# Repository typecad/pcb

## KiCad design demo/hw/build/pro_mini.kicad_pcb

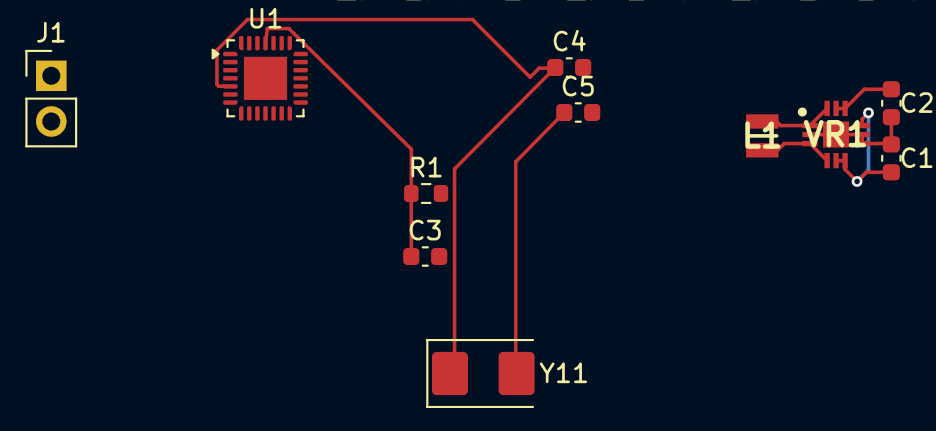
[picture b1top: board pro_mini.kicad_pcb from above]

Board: 2 copper layers, 11 parts (0 on the bottom side), 10 nets.

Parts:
C1: 22 uF; C_0603_1608Metric
C2: 10 uF; C_0603_1608Metric
C3: 100nF; C_0603_1608Metric
C4, C5: 22pF; C_0603_1608Metric
J1: PinHeader_1x02_P2.54mm_Vertical
L1: 1 µH; 1285ASH1R0MP2
R1: 10k; R_0603_1608Metric
U1: QFN-28-1EP_4x4mm_P0.45mm_EP2.4x2.4mm
VR1: QFN50P300X300X75-13N-D
Y11: Crystal_SMD_5032-2Pin_5.0x3.2mm

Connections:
net1: C1.2, VR1.5, VR1.6
net2: C1.1, C2.2, VR1.2, VR1.7, VR1.8, VR1.13
net3: L1.1, VR1.3, VR1.4
net4: L1.2, VR1.1, VR1.12
net5: C2.1, VR1.10, VR1.11
net6: J1.1, R1.2, U1.3, U1.16
net7: C3.2, C4.2, C5.2, J1.2, U1.4, U1.18, U1.29
net8: C3.1, R1.1, U1.25
net11: C4.1, U1.5, Y11.1
net12: C5.1, U1.6, Y11.2
